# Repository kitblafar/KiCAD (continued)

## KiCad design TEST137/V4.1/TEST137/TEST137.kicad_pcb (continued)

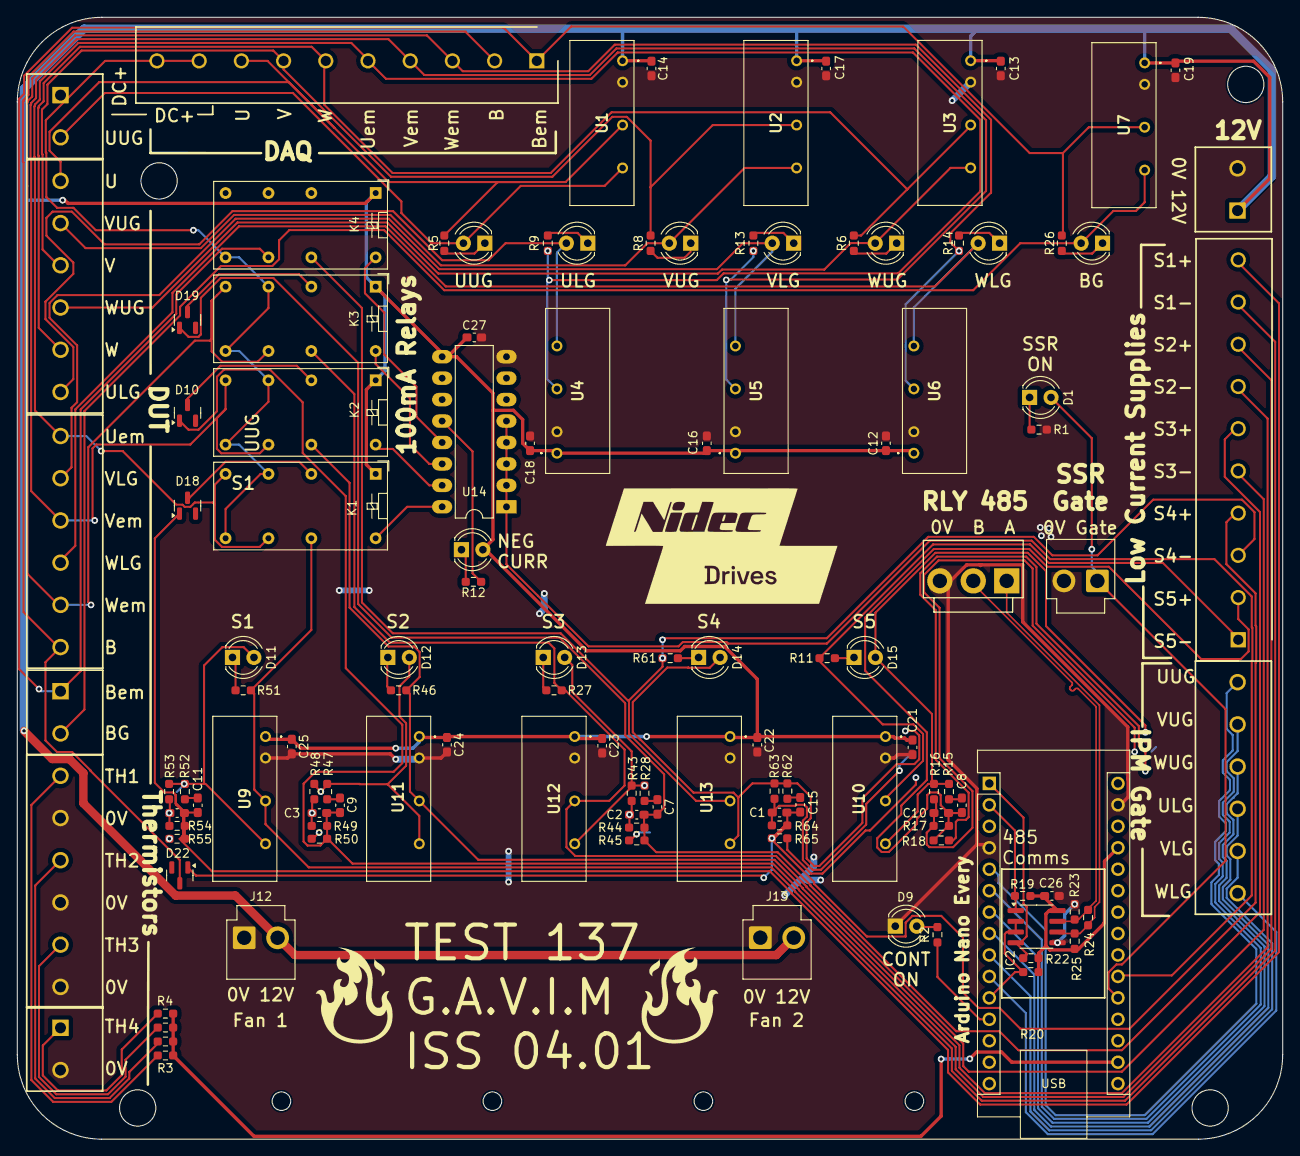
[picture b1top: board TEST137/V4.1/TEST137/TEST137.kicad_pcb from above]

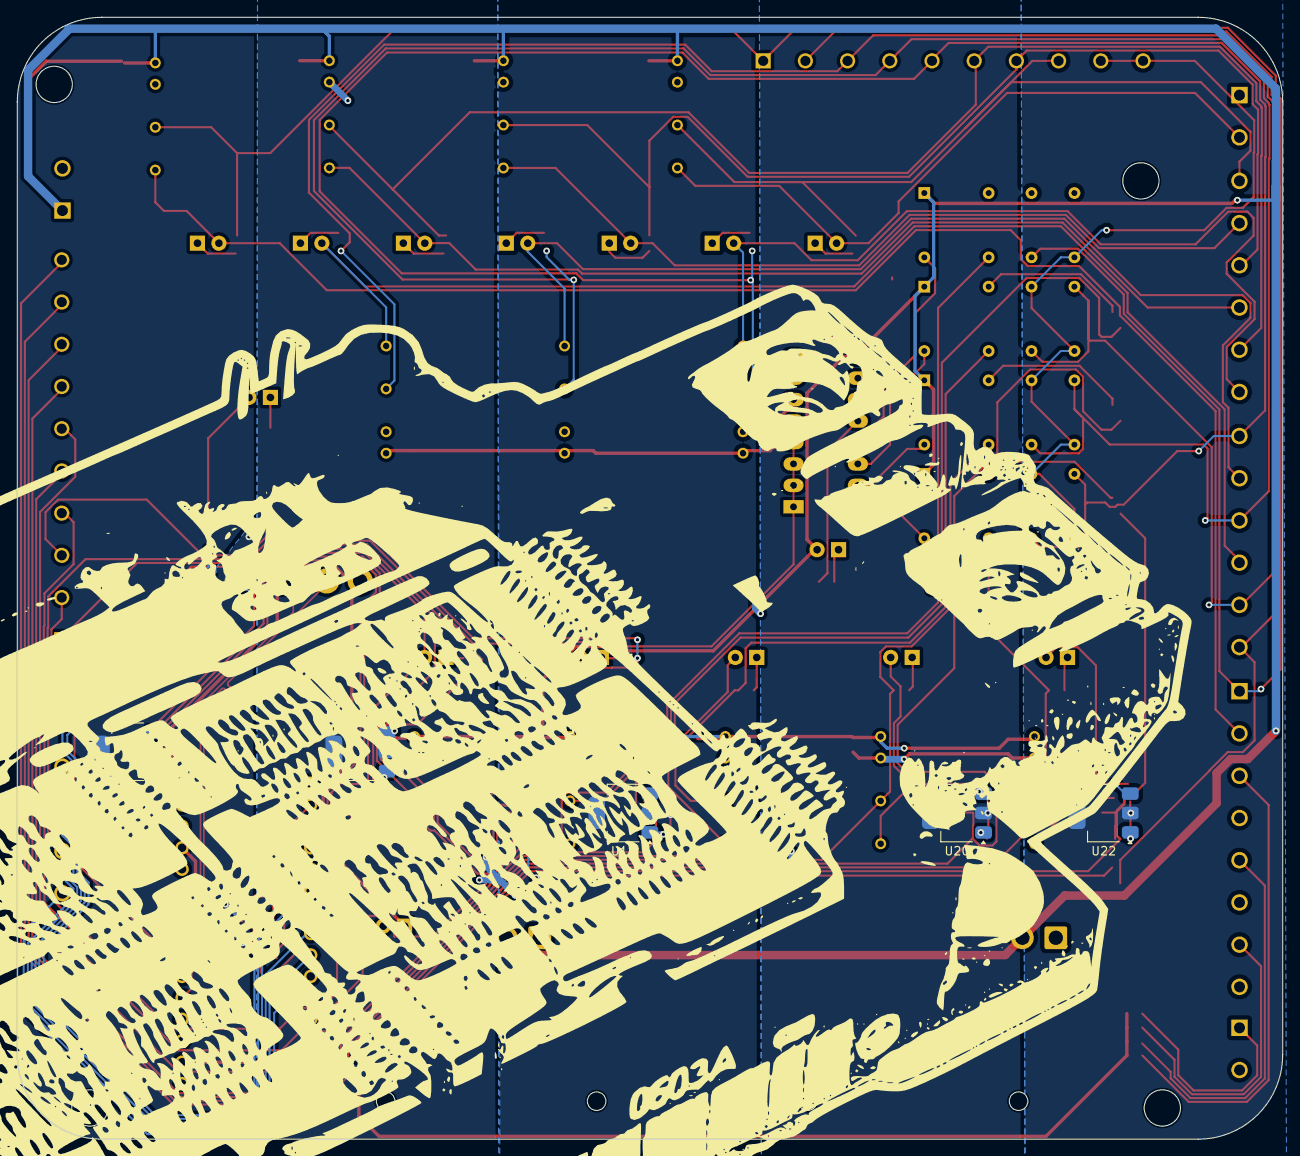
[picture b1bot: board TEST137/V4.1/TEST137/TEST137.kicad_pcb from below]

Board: 2 copper layers, 149.9 x 132.9 mm, 126 parts (5 on the bottom side), 91 nets.

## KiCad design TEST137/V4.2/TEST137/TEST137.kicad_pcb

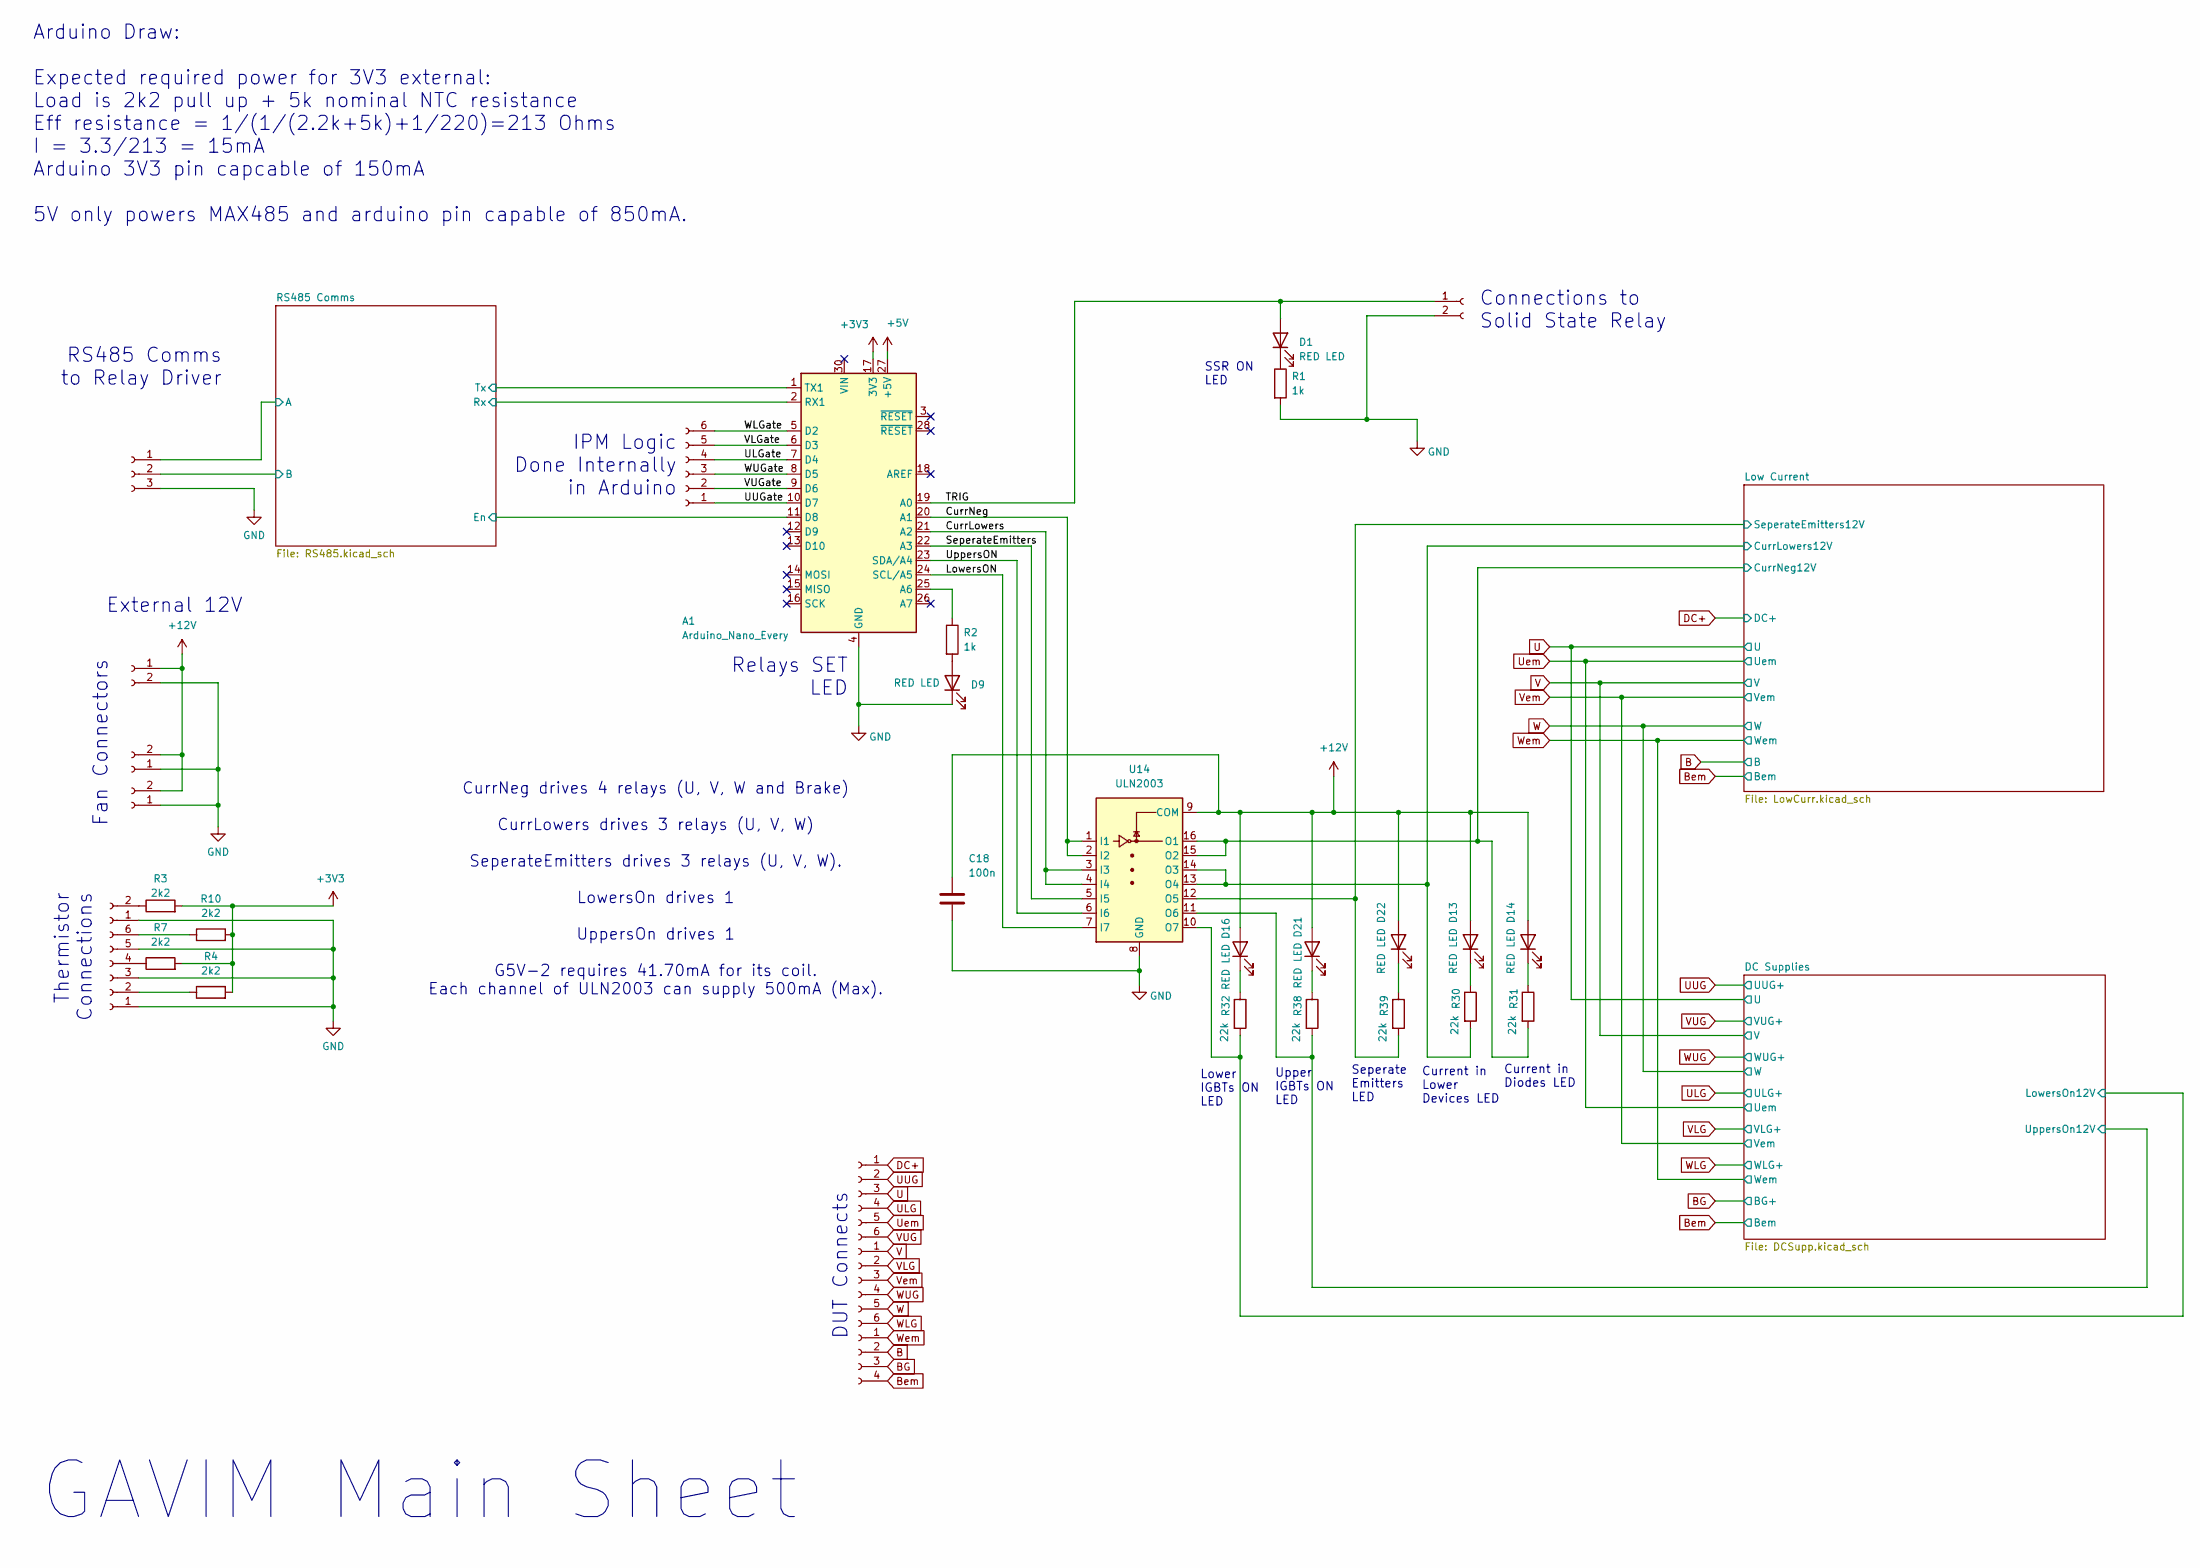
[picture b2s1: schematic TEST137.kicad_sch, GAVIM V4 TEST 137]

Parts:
A1: Arduino_Nano_Every; Arduino_Nano
C18: 100n; C_0603_1608Metric_Pad1.08x0.95mm_HandSolder
D1, D9, D13, D14, D16, D21, D22: RED LED; LED_D4.0mm
J1, J2, J4, J5: Conn_01x06_Socket; TB00150006BE
J3: Conn_01x06_Socket; TB00150004BE
J6, J11: Conn_01x02_Socket; CUI_TB001-500-02BE
J8, J12, J13: Conn_01x02_Socket; JST_VH_B2P-VH_1x02_P3.96mm_Vertical
J9: Conn_01x03_Socket; B3P-VH
R1, R2: 1k; R_0603_1608Metric_Pad0.98x0.95mm_HandSolder
R3, R4, R7, R10: 2k2; R_0603_1608Metric_Pad0.98x0.95mm_HandSolder
R30, R31, R32, R38, R39: 22k; R_0603_1608Metric_Pad0.98x0.95mm_HandSolder
U14: ULN2003; DIP-16_W7.62mm_LongPads

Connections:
+3V3: A1.17 (3V3), R3.2, R4.2, R7.2, R10.2
+5V: A1.27 (+5V); also elsewhere on the board
+12V: C18.1, D13.2 (A), D14.2 (A), D16.2 (A), D21.2 (A), D22.2 (A), J11.1, J12.2, J13.2, U14.9 (COM); also elsewhere on the board
/CurrLowers: A1.21 (A2), U14.3 (I3), U14.4 (I4)
/CurrNeg: A1.20 (A1), U14.1 (I1), U14.2 (I2)
/DC Supplies/LowersOn12V: R32.2, U14.10 (O7); also elsewhere on the board
/DC Supplies/UppersOn12V: R38.2, U14.11 (O6); also elsewhere on the board
/Low Current/CurrLowers12V: R30.2, U14.13 (O4), U14.14 (O3); also elsewhere on the board
/Low Current/CurrNeg12V: R31.2, U14.15 (O2), U14.16 (O1); also elsewhere on the board
/Low Current/SeperateEmitters12V: R39.2, U14.12 (O5); also elsewhere on the board
/LowersON: A1.24 (SCL/A5), U14.7 (I7)
/RS485 Comms/B+: J9.2; also elsewhere on the board
/RS485 Comms/B-: J9.1; also elsewhere on the board
/RS485 Comms/En: A1.11 (D8); also elsewhere on the board
/RS485 Comms/Rx: A1.2 (RX1); also elsewhere on the board
/RS485 Comms/Tx: A1.1 (TX1); also elsewhere on the board
/SeperateEmitters: A1.22 (A3), U14.5 (I5)
/TRIG: A1.19 (A0), D1.2 (A), J8.1
/ULGate: A1.7 (D4), J1.4
/UUGate: A1.10 (D7), J1.1
/UppersON: A1.23 (SDA/A4), U14.6 (I6)
/VLGate: A1.6 (D3), J1.5
/VUGate: A1.9 (D6), J1.2
/WLGate: A1.5 (D2), J1.6
/WUGate: A1.8 (D5), J1.3
B: J3.2; also elsewhere on the board
BG: J3.3; also elsewhere on the board
Bem: J3.4; also elsewhere on the board
DC+: J2.1; also elsewhere on the board
GND: A1.4 (GND), A1.29 (GND), C18.2, D9.1 (K), J5.1, J5.3, J5.5, J6.1, J8.2, J9.3, J11.2, J12.1, J13.1, R1.2, U14.8 (GND); also elsewhere on the board
unnamed: A1.25 (A6), R2.1
unnamed: D1.1 (K), R1.1
unnamed: D9.2 (A), R2.2
unnamed: D13.1 (K), R30.1
unnamed: D14.1 (K), R31.1
unnamed: D16.1 (K), R32.1
unnamed: D21.1 (K), R38.1
unnamed: D22.1 (K), R39.1
unnamed: J5.2, R4.1
unnamed: J5.4, R7.1
unnamed: J5.6, R10.1
unnamed: J6.2, R3.1
U: J2.3; also elsewhere on the board
ULG: J2.4; also elsewhere on the board
UUG: J2.2; also elsewhere on the board
Uem: J2.5; also elsewhere on the board
V: J4.1; also elsewhere on the board
VLG: J4.2; also elsewhere on the board
VUG: J2.6; also elsewhere on the board
Vem: J4.3; also elsewhere on the board
W: J4.5; also elsewhere on the board
WLG: J4.6; also elsewhere on the board
WUG: J4.4; also elsewhere on the board
Wem: J3.1; also elsewhere on the board

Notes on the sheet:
GAVIM Main Sheet
Current in Diodes LED
CurrNeg drives 4 relays (U, V, W and Brake) CurrLowers drives 3 relays (U, V, W) SeperateEmitters drives 3 relays (U, V, W). LowersOn drives 1 UppersOn drives 1 G5V-2 requires 41.70mA for its coil. Each channel of ULN2003 can supply 500mA (Max).
Seperate Emitters LED
IPM Logic Done Internally in Arduino
External 12V
Fan Connectors
Upper IGBTs ON LED
RS485 Comms to Relay Driver
DUT Connects
SSR ON LED
Arduino Draw: Expected required power for 3V3 external: Load is 2k2 pull up + 5k nominal NTC resistance Eff resistance = 1/(1/(2.2k+5k)+1/220)=213 Ohms I = 3.3/213 = 15mA Arduino 3V3 pin capcable of 150mA 5V only powers MAX485 and arduino pin capable of 850mA.
Lower IGBTs ON LED
Current in Lower Devices LED
Relays SET LED
Connections to Solid State Relay
Thermistor Connections

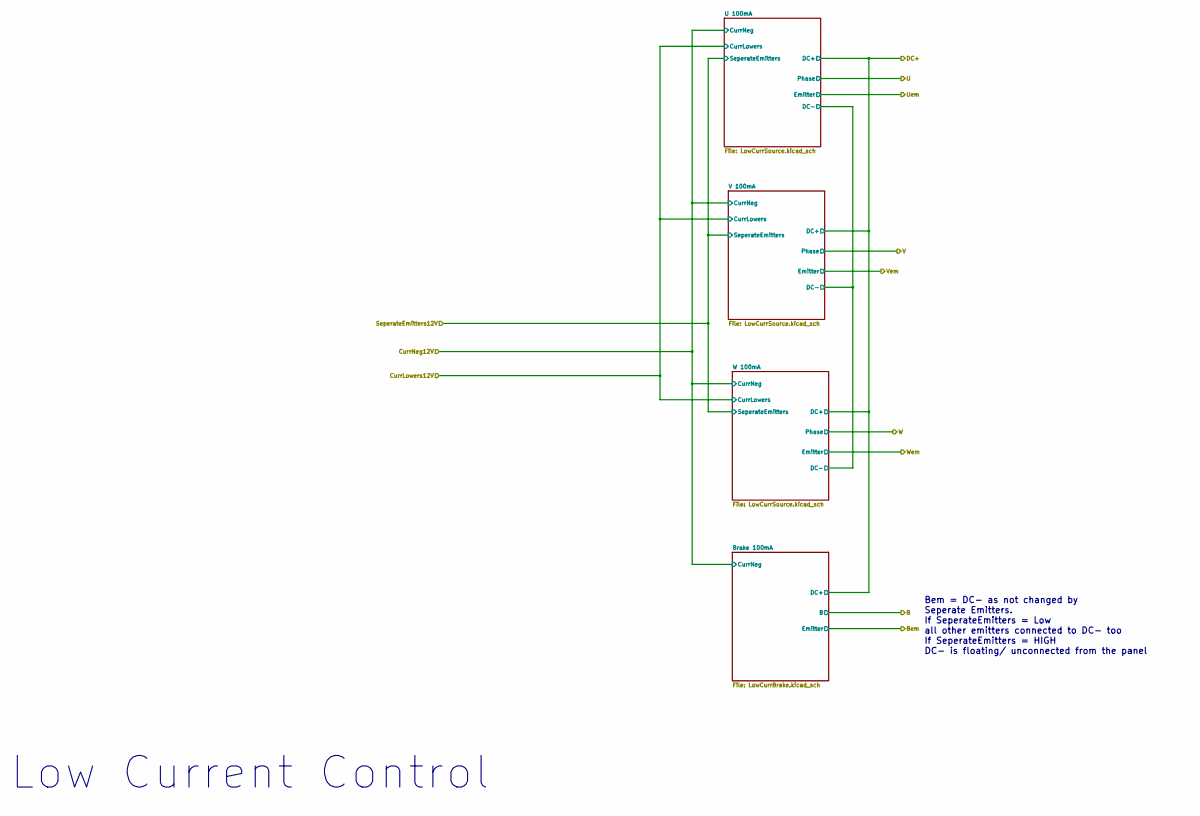
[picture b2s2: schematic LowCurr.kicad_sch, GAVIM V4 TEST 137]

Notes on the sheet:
Bem = DC- as not changed by Seperate Emitters. If SeperateEmitters = Low all other emitters connected to DC- too If SeperateEmitters = HIGH DC- is floating/ unconnected from the panel
Low Current Control

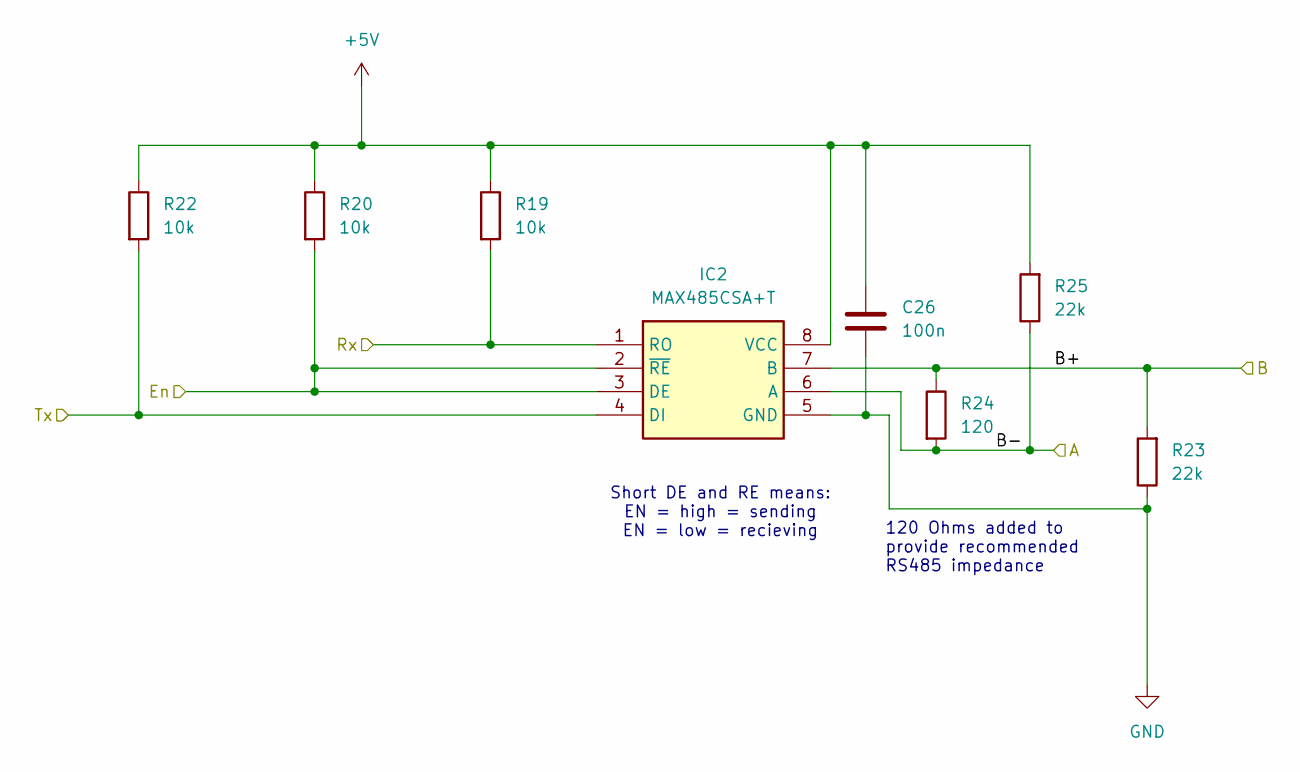
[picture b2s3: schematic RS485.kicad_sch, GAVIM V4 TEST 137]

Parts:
C26: 100n; C_0603_1608Metric_Pad1.08x0.95mm_HandSolder
IC2: MAX485CSA+T; SOIC-8_3.9x4.9mm_P1.27mm; Mouser Part Number 700-MAX485CSAT
R19, R20, R22: 10k; R_0603_1608Metric_Pad0.98x0.95mm_HandSolder
R23, R25: 22k; R_0603_1608Metric_Pad0.98x0.95mm_HandSolder
R24: 120; R_0603_1608Metric_Pad0.98x0.95mm_HandSolder

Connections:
+5V: C26.1, IC2.8 (VCC), R19.1, R20.1, R22.1, R25.2; also elsewhere on the board
/RS485 Comms/B+: IC2.7 (B), R23.2, R24.1; also elsewhere on the board
/RS485 Comms/B-: IC2.6 (A), R24.2, R25.1; also elsewhere on the board
/RS485 Comms/En: IC2.2 (~RE), IC2.3 (DE), R20.2; also elsewhere on the board
/RS485 Comms/Rx: IC2.1 (RO), R19.2; also elsewhere on the board
/RS485 Comms/Tx: IC2.4 (DI), R22.2; also elsewhere on the board
GND: C26.2, IC2.5 (GND), R23.1; also elsewhere on the board

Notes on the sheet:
Short DE and RE means: EN = high = sending EN = low = recieving
120 Ohms added to provide recommended RS485 impedance

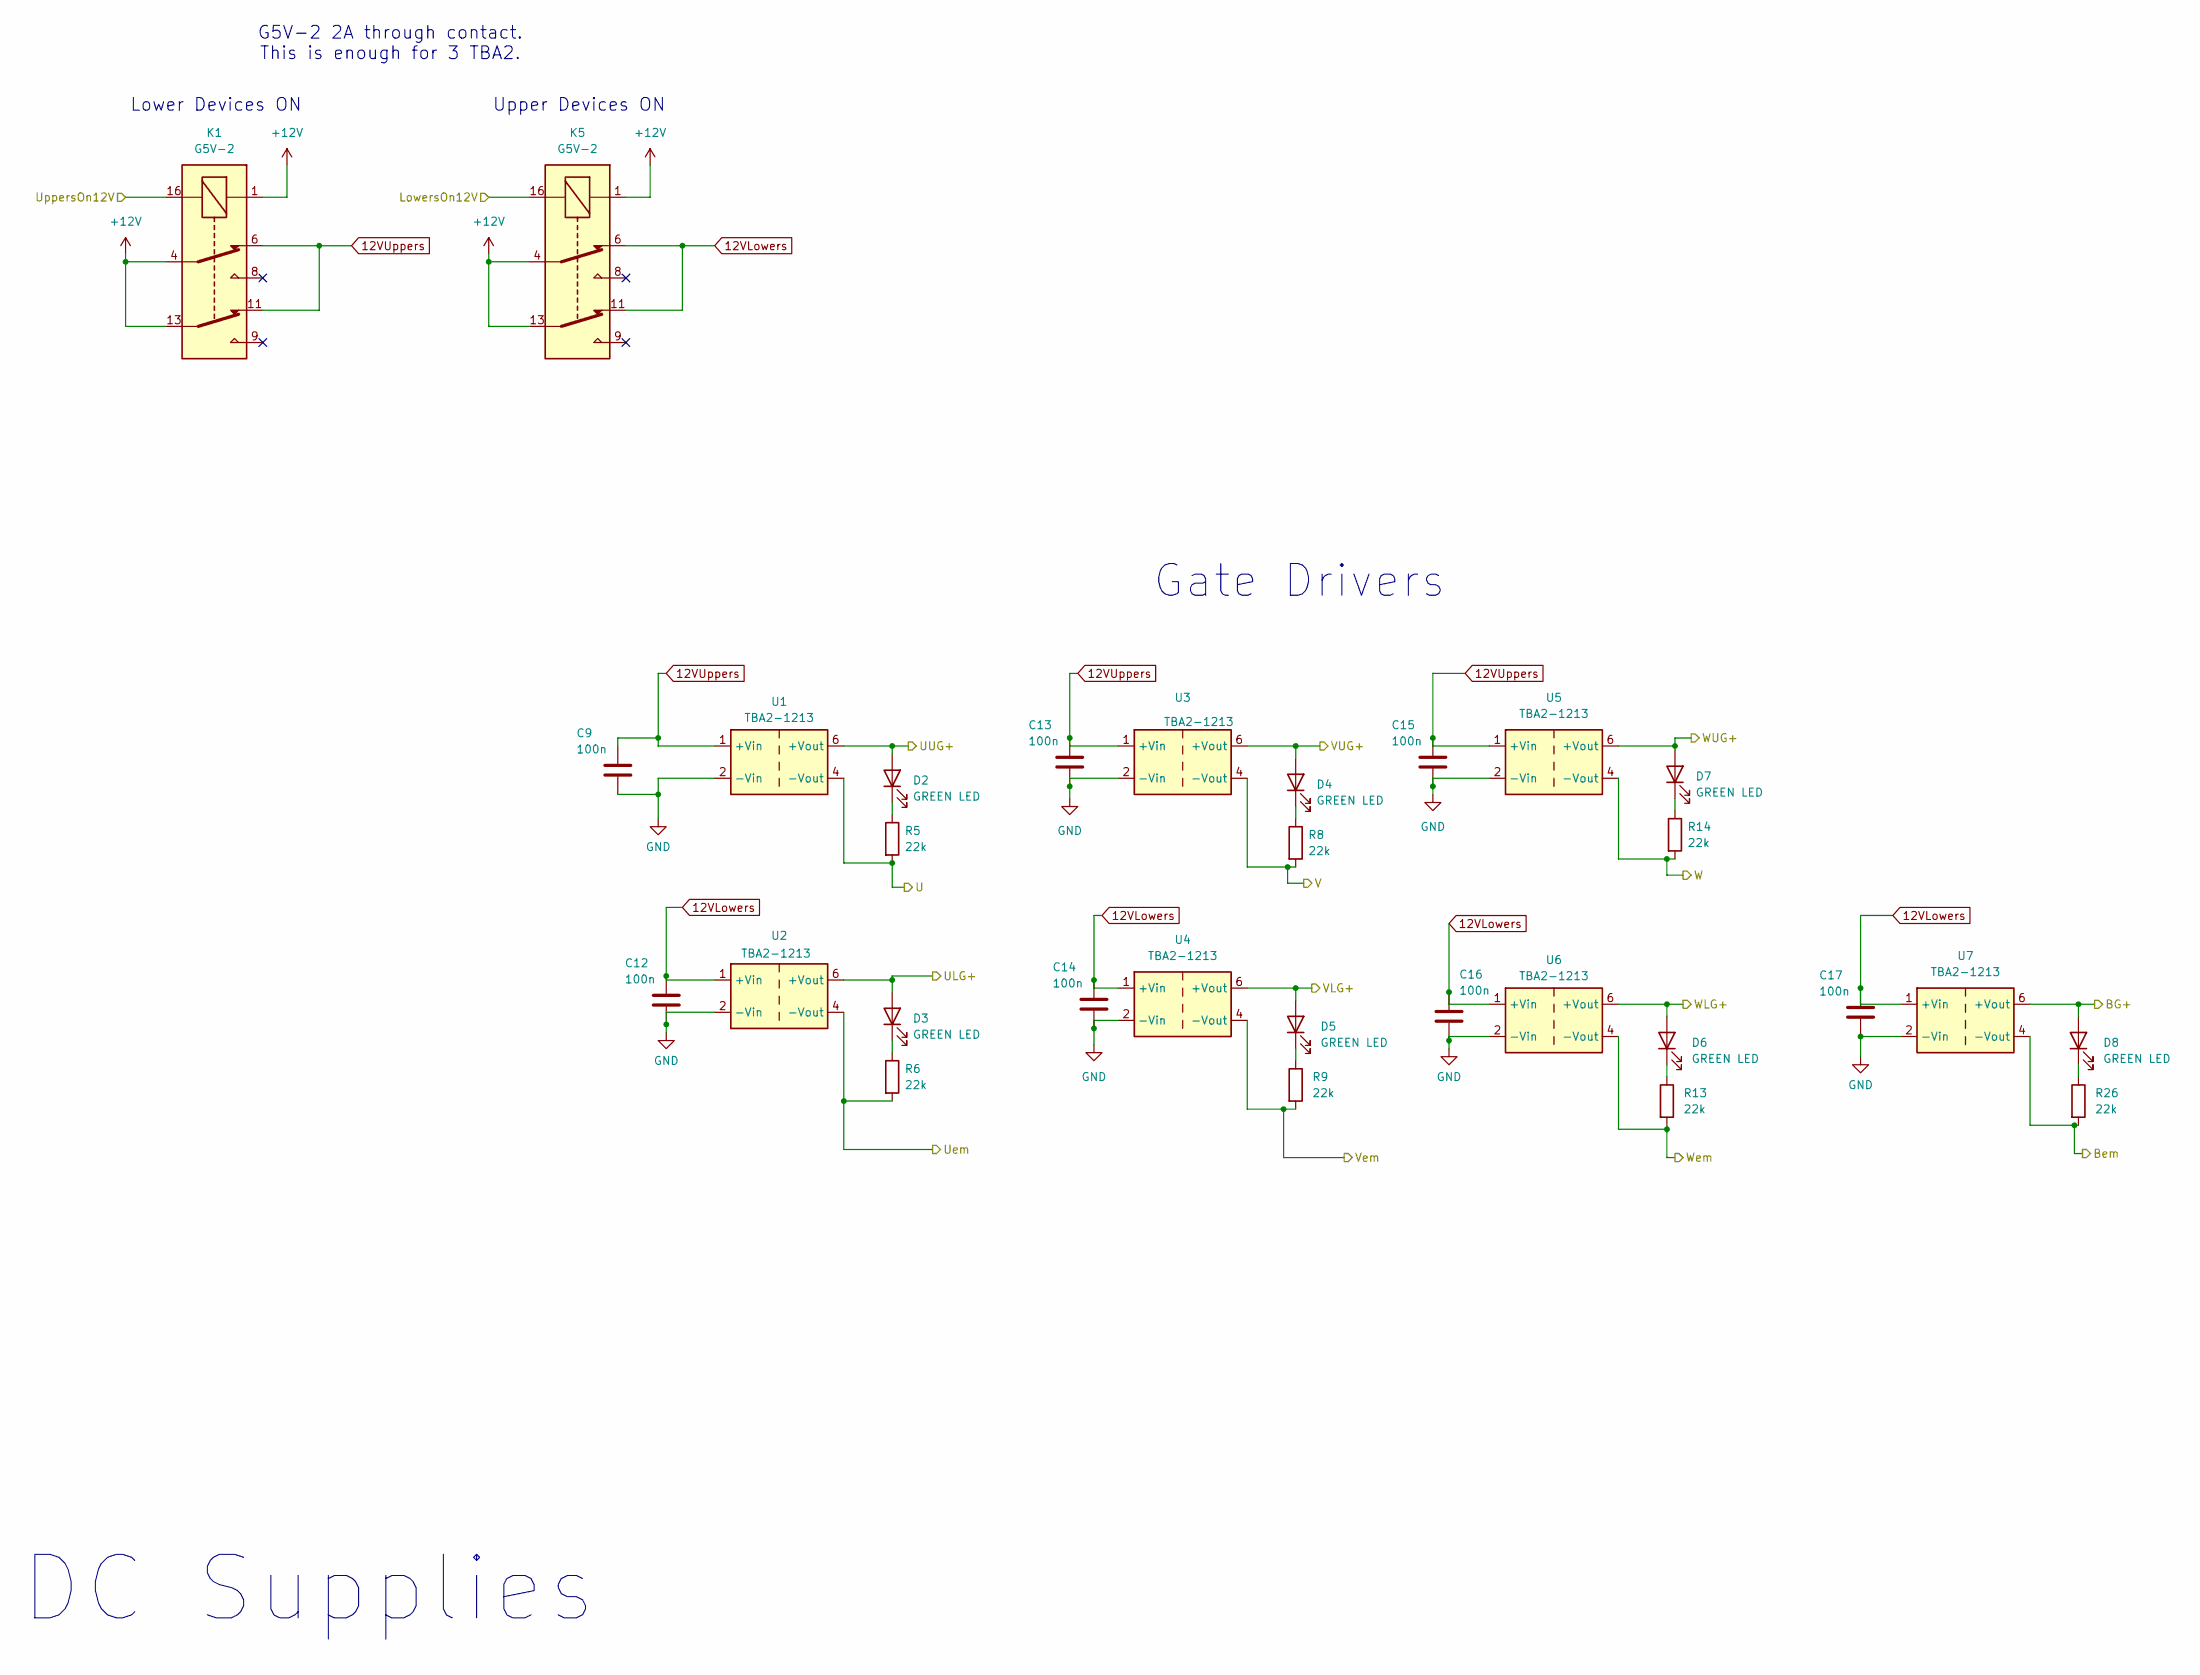
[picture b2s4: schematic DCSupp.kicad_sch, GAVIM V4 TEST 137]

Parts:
C9, C12, C13, C14, C15, C16, C17: 100n; C_0603_1608Metric_Pad1.08x0.95mm_HandSolder
D2, D3, D4, D5, D6, D7, D8: GREEN LED; LED_D4.0mm
K1, K5: G5V-2; Relay_DPDT_Omron_G5V-2
R5, R6, R8, R9, R13, R14, R26: 22k; R_0603_1608Metric_Pad0.98x0.95mm_HandSolder
U1, U2, U3, U4, U5, U6, U7: TBA2-1213; TBA21213

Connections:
12VLowers: C12.1, C14.1, C16.1, C17.1, K5.6, K5.11, U2.1 (+Vin), U4.1 (+Vin), U6.1 (+Vin), U7.1 (+Vin)
12VUppers: C9.1, C13.1, C15.1, K1.6, K1.11, U1.1 (+Vin), U3.1 (+Vin), U5.1 (+Vin)
+12V: K1.1, K1.4, K1.13, K5.1, K5.4, K5.13; also elsewhere on the board
/DC Supplies/LowersOn12V: K5.16; also elsewhere on the board
/DC Supplies/UppersOn12V: K1.16; also elsewhere on the board
BG: D8.2 (A), U7.6 (+Vout); also elsewhere on the board
Bem: R26.2, U7.4 (-Vout); also elsewhere on the board
GND: C9.2, C12.2, C13.2, C14.2, C15.2, C16.2, C17.2, U1.2 (-Vin), U2.2 (-Vin), U3.2 (-Vin), U4.2 (-Vin), U5.2 (-Vin), U6.2 (-Vin), U7.2 (-Vin); also elsewhere on the board
unnamed: D2.1 (K), R5.1
unnamed: D3.1 (K), R6.1
unnamed: D4.1 (K), R8.1
unnamed: D5.1 (K), R9.1
unnamed: D6.1 (K), R13.1
unnamed: D7.1 (K), R14.1
unnamed: D8.1 (K), R26.1
U: R5.2, U1.4 (-Vout); also elsewhere on the board
ULG: D3.2 (A), U2.6 (+Vout); also elsewhere on the board
UUG: D2.2 (A), U1.6 (+Vout); also elsewhere on the board
Uem: R6.2, U2.4 (-Vout); also elsewhere on the board
V: R8.2, U3.4 (-Vout); also elsewhere on the board
VLG: D5.2 (A), U4.6 (+Vout); also elsewhere on the board
VUG: D4.2 (A), U3.6 (+Vout); also elsewhere on the board
Vem: R9.2, U4.4 (-Vout); also elsewhere on the board
W: R14.2, U5.4 (-Vout); also elsewhere on the board
WLG: D6.2 (A), U6.6 (+Vout); also elsewhere on the board
WUG: D7.2 (A), U5.6 (+Vout); also elsewhere on the board
Wem: R13.2, U6.4 (-Vout); also elsewhere on the board

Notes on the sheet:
Upper Devices ON
Gate Drivers
DC Supplies
Lower Devices ON
G5V-2 2A through contact. This is enough for 3 TBA2.

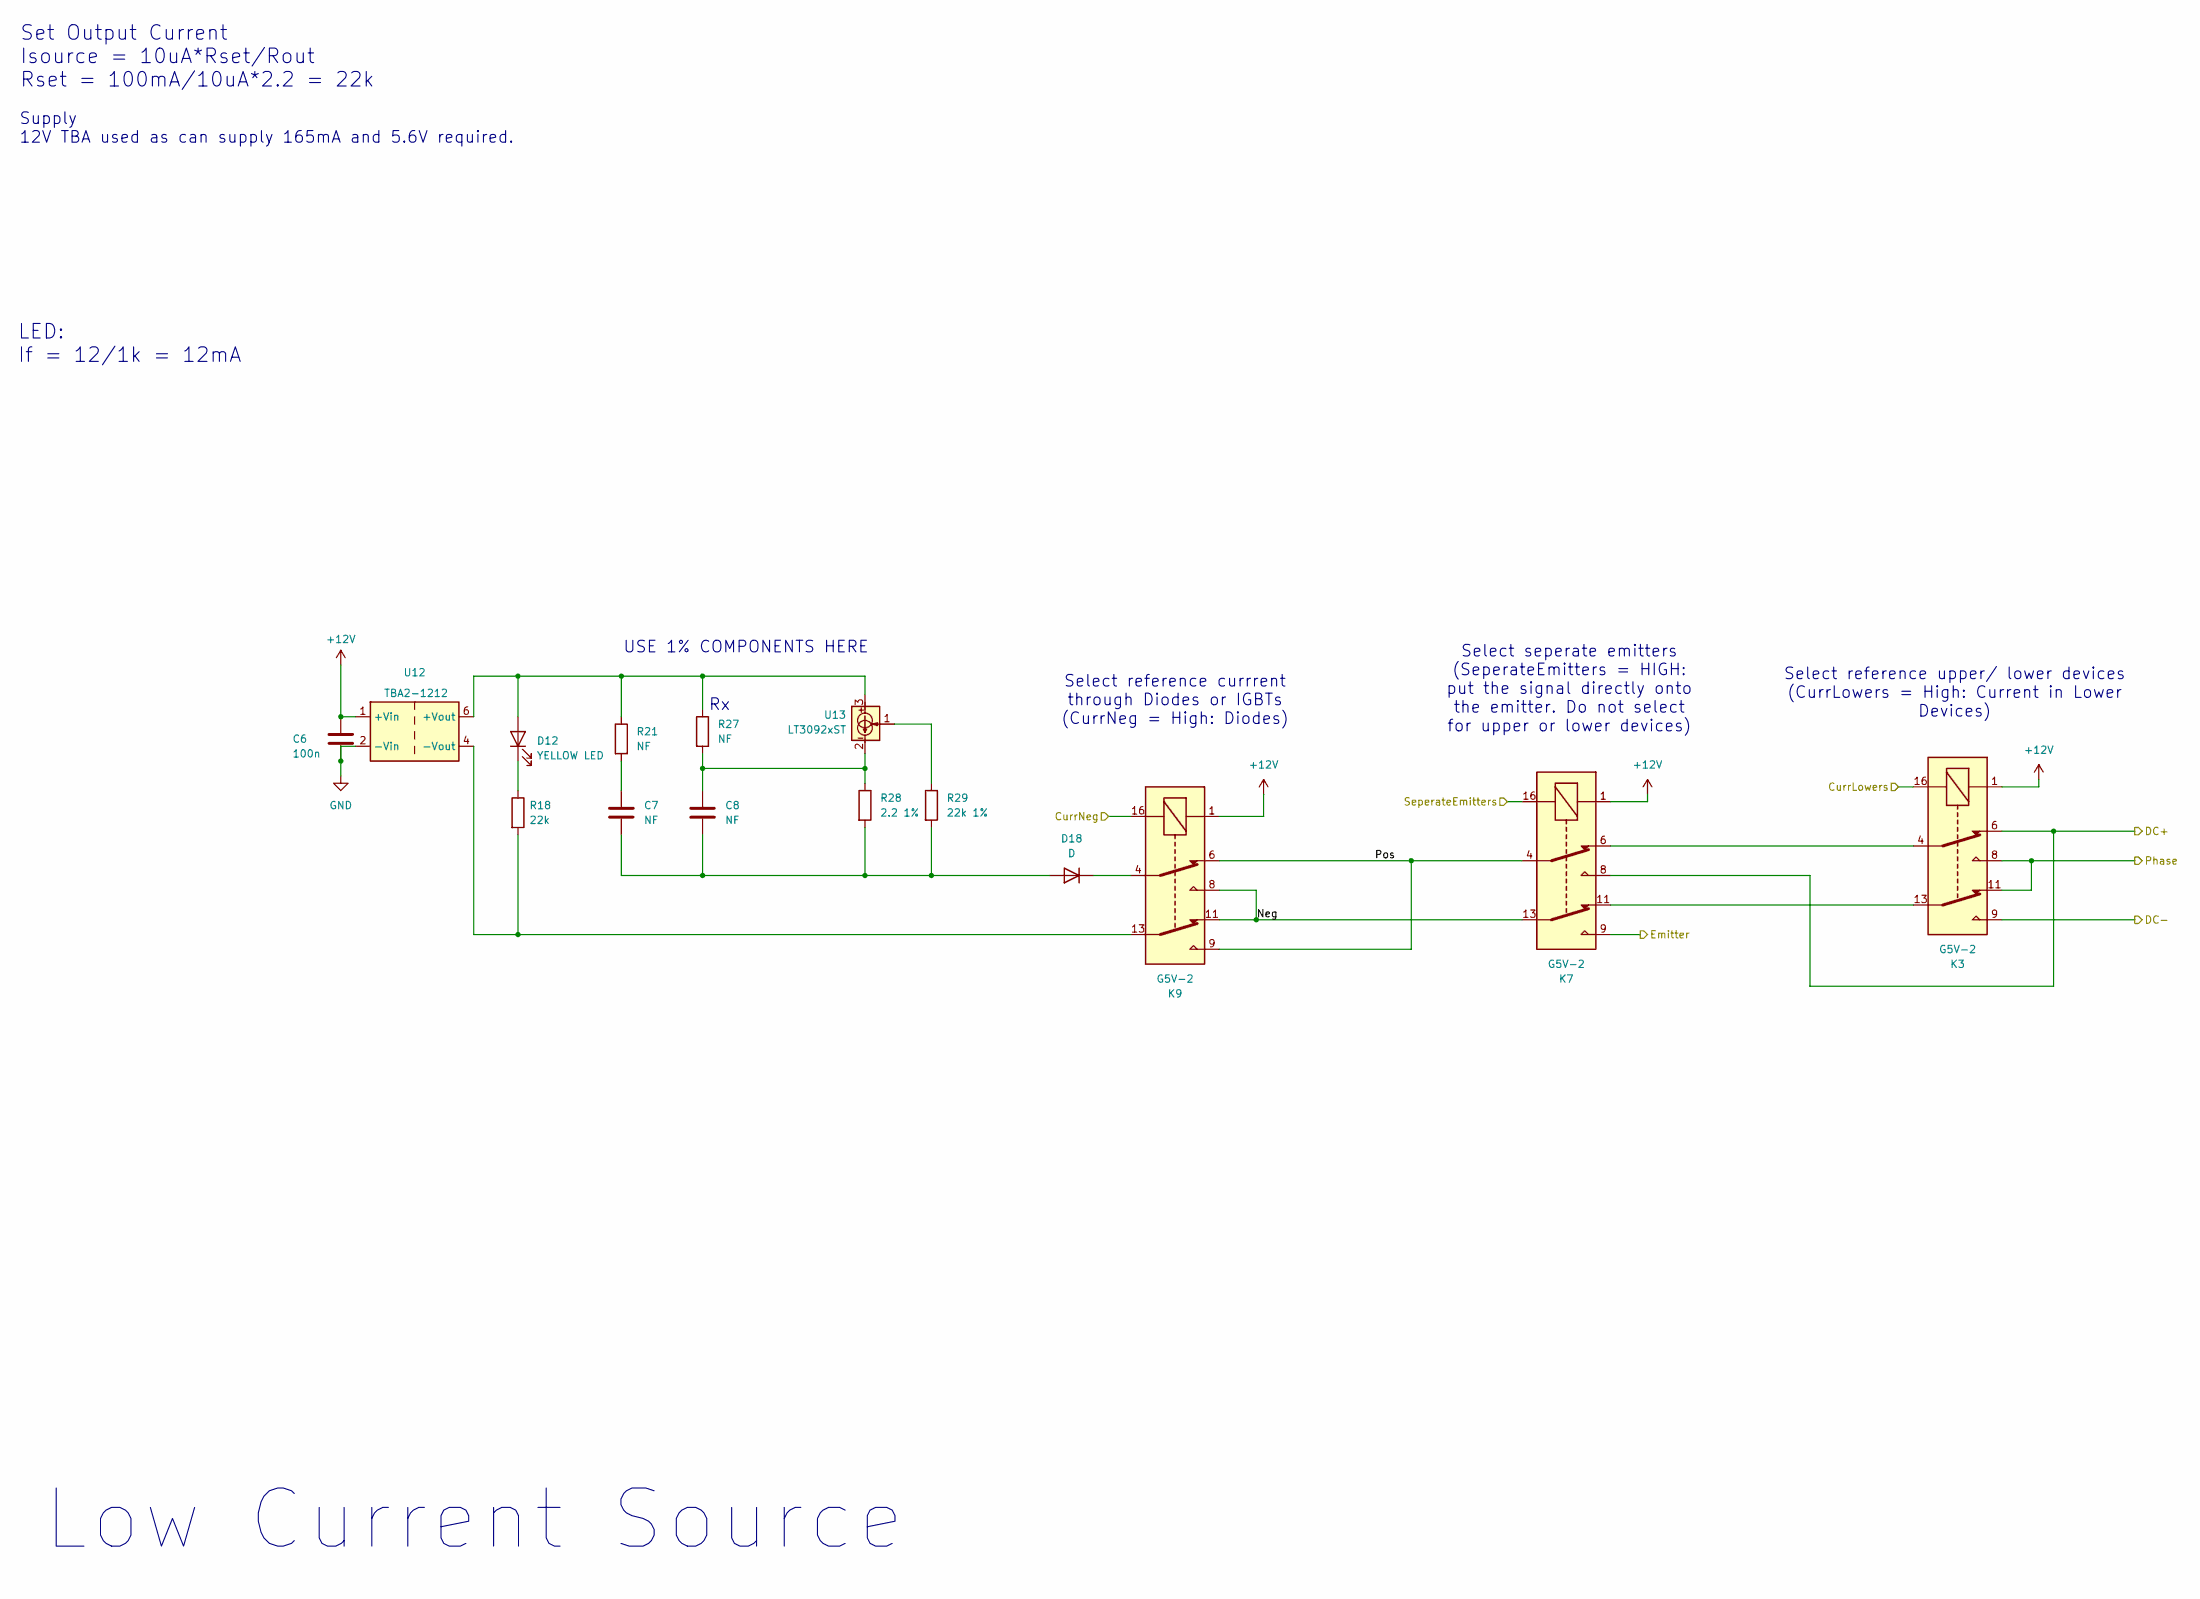
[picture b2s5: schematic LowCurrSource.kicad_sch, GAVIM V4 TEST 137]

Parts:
C6: 100n; C_0603_1608Metric_Pad1.08x0.95mm_HandSolder
C7, C8: NF; C_0603_1608Metric_Pad1.08x0.95mm_HandSolder
D12: YELLOW LED; LED_D4.0mm
D18: D; BAS16
K3, K7, K9: G5V-2; Relay_DPDT_Omron_G5V-2
R18: 22k; R_0603_1608Metric_Pad0.98x0.95mm_HandSolder
R21, R27: NF; R_0603_1608Metric_Pad0.98x0.95mm_HandSolder
R28: 2.2 1%; R_0603_1608Metric_Pad0.98x0.95mm_HandSolder
R29: 22k 1%; R_0603_1608Metric_Pad0.98x0.95mm_HandSolder
U12: TBA2-1212; TBA21213
U13: LT3092xST; SOT-223-3_TabPin2

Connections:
+12V: C6.1, K3.1, K7.1, K9.1, U12.1 (+Vin); also elsewhere on the board
/Low Current/CurrLowers12V: K3.16; also elsewhere on the board
/Low Current/CurrNeg12V: K9.16; also elsewhere on the board
/Low Current/SeperateEmitters12V: K7.16; also elsewhere on the board
/Low Current/U 100mA/DC-: K3.9; also elsewhere on the board
/Low Current/W 100mA/Neg: K7.13, K9.8, K9.11
/Low Current/W 100mA/Pos: K7.4, K9.6, K9.9
DC+: K3.6, K7.8; also elsewhere on the board
GND: C6.2, U12.2 (-Vin); also elsewhere on the board
unnamed: C7.1, R21.2
unnamed: C8.1, R27.2, R28.1, U13.2
unnamed: D12.2 (A), R21.1, R27.1, U12.6 (+Vout), U13.3
unnamed: D12.1 (K), R18.1
unnamed: C7.2, C8.2, D18.2 (A), R28.2, R29.2
unnamed: D18.1 (K), K9.4
unnamed: K3.4, K7.6
unnamed: K3.13, K7.11
unnamed: R29.1, U13.1
unnamed: K9.13, R18.2, U12.4 (-Vout)
W: K3.8, K3.11; also elsewhere on the board
Wem: K7.9; also elsewhere on the board

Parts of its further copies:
C1, C25: 100n; C_0603_1608Metric_Pad1.08x0.95mm_HandSolder
C2, C3, C4, C11: NF; C_0603_1608Metric_Pad1.08x0.95mm_HandSolder
D10, D11: YELLOW LED; LED_D4.0mm
D17, D19: D; BAS16
K2, K4, K6, K8, K10, K12: G5V-2; Relay_DPDT_Omron_G5V-2
R11, R51: 22k; R_0603_1608Metric_Pad0.98x0.95mm_HandSolder
R12, R15, R52, R53: NF; R_0603_1608Metric_Pad0.98x0.95mm_HandSolder
R16, R54: 2.2 1%; R_0603_1608Metric_Pad0.98x0.95mm_HandSolder
R17, R55: 22k 1%; R_0603_1608Metric_Pad0.98x0.95mm_HandSolder
U9, U10: TBA2-1212; TBA21213
U11, U22: LT3092xST; SOT-223-3_TabPin2

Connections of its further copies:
+12V: C1.1, C25.1, K2.1, K4.1, K6.1, K8.1, K10.1, K12.1, U9.1 (+Vin), U10.1 (+Vin); also elsewhere on the board
/Low Current/CurrLowers12V: K2.16, K4.16; also elsewhere on the board
/Low Current/CurrNeg12V: K8.16, K10.16; also elsewhere on the board
/Low Current/SeperateEmitters12V: K6.16, K12.16; also elsewhere on the board
/Low Current/U 100mA/DC-: K2.9, K4.9; also elsewhere on the board
/Low Current/U 100mA/Neg: K10.8, K10.11, K12.13
/Low Current/U 100mA/Pos: K10.6, K10.9, K12.4
/Low Current/V 100mA/Neg: K6.13, K8.8, K8.11
/Low Current/V 100mA/Pos: K6.4, K8.6, K8.9
DC+: K2.6, K4.6, K6.8, K12.8; also elsewhere on the board
GND: C1.2, C25.2, U9.2 (-Vin), U10.2 (-Vin); also elsewhere on the board
unnamed: C2.1, R12.2
unnamed: C3.1, R15.2, R16.1, U11.2
unnamed: C4.1, R53.2, R54.1, U22.2
unnamed: C11.1, R52.2
unnamed: D10.2 (A), R12.1, R15.1, U10.6 (+Vout), U11.3
unnamed: D10.1 (K), R11.1
unnamed: D11.2 (A), R52.1, R53.1, U9.6 (+Vout), U22.3
unnamed: D11.1 (K), R51.1
unnamed: C2.2, C3.2, D17.2 (A), R16.2, R17.2
unnamed: D17.1 (K), K8.4
unnamed: C4.2, C11.2, D19.2 (A), R54.2, R55.2
unnamed: D19.1 (K), K10.4
unnamed: K2.4, K6.6
unnamed: K2.13, K6.11
unnamed: K4.4, K12.6
unnamed: K4.13, K12.11
unnamed: R17.1, U11.1
unnamed: R55.1, U22.1
unnamed: K10.13, R51.2, U9.4 (-Vout)
unnamed: K8.13, R11.2, U10.4 (-Vout)
U: K4.8, K4.11; also elsewhere on the board
Uem: K12.9; also elsewhere on the board
V: K2.8, K2.11; also elsewhere on the board
Vem: K6.9; also elsewhere on the board

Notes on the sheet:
Supply 12V TBA used as can supply 165mA and 5.6V required.
LED: If = 12/1k = 12mA
Select reference currrent through Diodes or IGBTs (CurrNeg = High: Diodes)
Select seperate emitters (SeperateEmitters = HIGH: put the signal directly onto the emitter. Do not select for upper or lower devices)
Select reference upper/ lower devices (CurrLowers = High: Current in Lower Devices)
Set Output Current Isource = 10uA*Rset/Rout Rset = 100mA/10uA*2.2 = 22k
USE 1% COMPONENTS HERE
Low Current Source
